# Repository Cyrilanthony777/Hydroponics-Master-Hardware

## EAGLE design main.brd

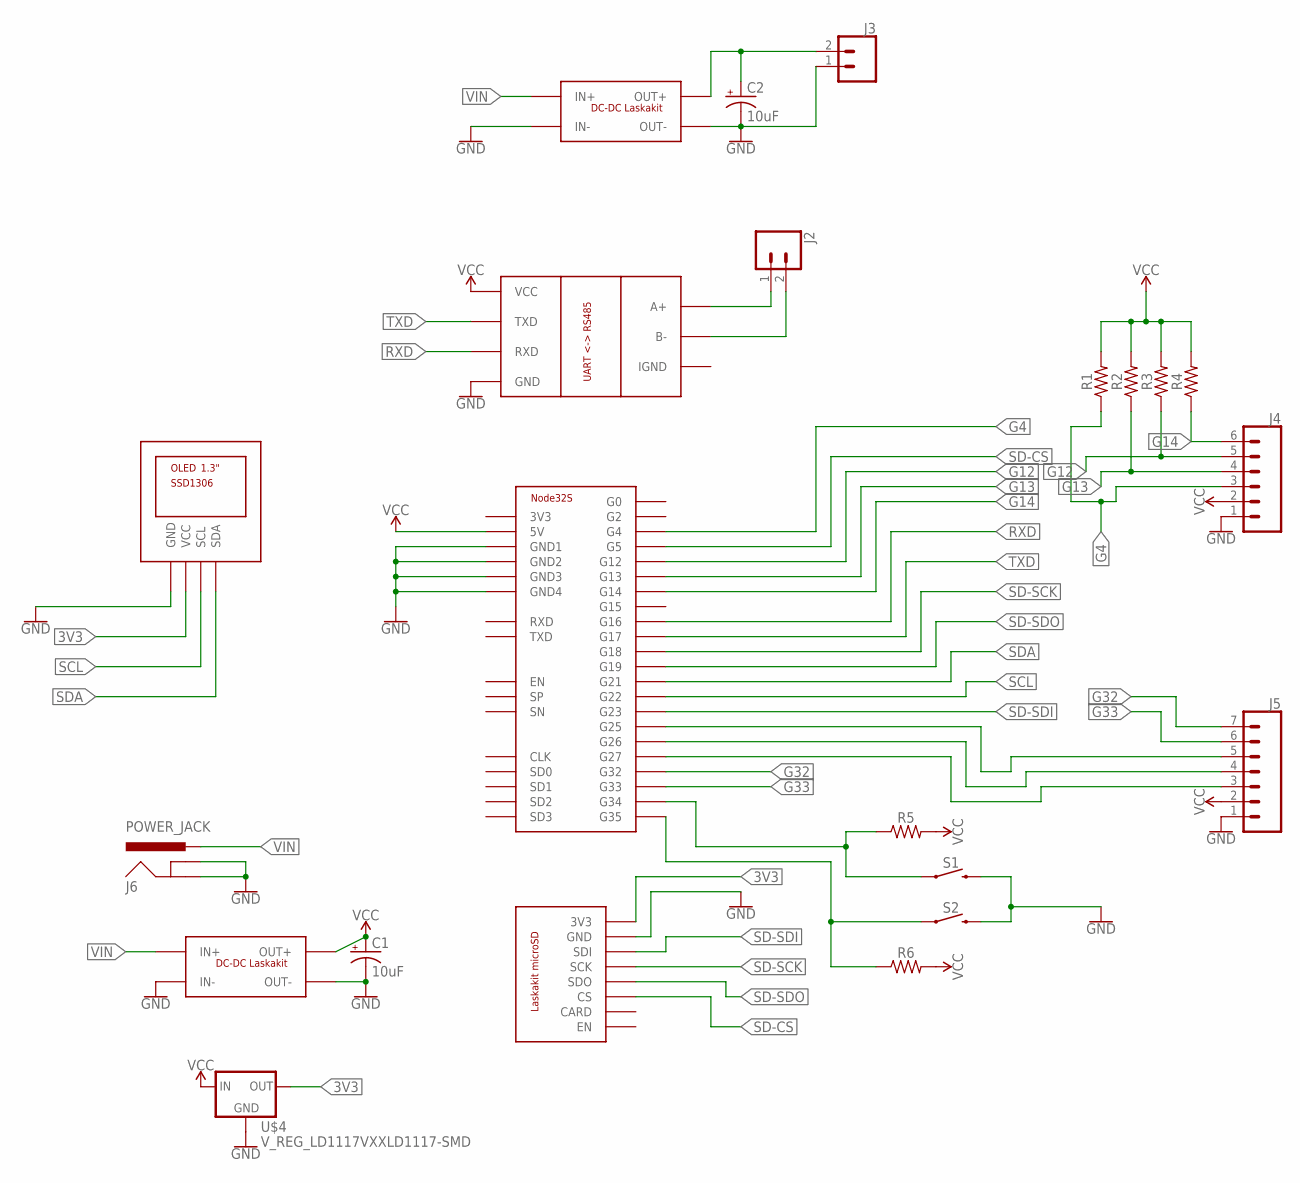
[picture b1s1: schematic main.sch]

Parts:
C1, C2: 10uF; CPOL-RADIAL-2.5MM-5MM
J2, J3: CONN_025MM; SCREWTERMINAL-5MM-2
J4: CONN_06NO_SILK_FEMALE_PTH; 1X06_NO_SILK
J5: CONN_07NO_SILK; 1X07_NO_SILK
J6: POWER_JACK; POWER_JACK_PTH
R1, R2, R3, R4, R5, R6: 0805
S1, S2: MOMENTARY-SWITCH-SPST-PTH-12MM; TACTILE_SWITCH_PTH_12MM
U$1: NODE32S
U$2: LASKAKIT_SDCARD; LASKAKIT_SD_MODULE
U$3, U$7: DC-DC-LASKAKIT; DC-DC-MODULE-LASKAKIT
U$4: V_REG_LD1117VXXLD1117-SMD; SOT223
U$5: RS485-UART-CONVERTER; RS485_MODULE
U$6: OLED_0.96_I2C; OLED_0.96

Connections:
3V3: U$2.P$1 (3V3), U$4.2 (OUT), U$6.P$2 (VCC)
G4: J4.3, R1.1, U$1.P$26 (G4)
G12: J4.5, R3.1, U$1.P$13 (G12)
G13: J4.4, R2.1, U$1.P$15 (G13)
G14: J4.6, R4.1, U$1.P$12 (G14)
G32: J5.7, U$1.P$7 (G32)
G33: J5.6, U$1.P$8 (G33)
GND: C1.2 (-), C2.2 (-), J3.1, J4.1, J5.1, J6.GND, J6.GNDBREAK, S1.3 (2), S2.3 (2), U$1.P$14 (GND1), U$1.P$18 (GND2), U$1.P$32 (GND3), U$1.P$38 (GND4), U$2.P$2 (GND), U$3.IN-, U$3.OUT-, U$4.1 (GND), U$5.GND, U$6.P$1 (GND), U$7.IN-, U$7.OUT-
unnamed: J2.1, U$5.A+
unnamed: J2.2, U$5.B-
unnamed: J5.5, U$1.P$9 (G25)
unnamed: J5.4, U$1.P$10 (G26)
unnamed: J5.3, U$1.P$11 (G27)
unnamed: C2.1 (+), J3.2, U$7.OUT+
unnamed: R6.1, S2.1, U$1.P$6 (G35)
unnamed: R5.1, S1.1, U$1.P$5 (G34)
RXD: U$1.P$27 (G16), U$5.RXD
SCL: U$1.P$36 (G22), U$6.P$3 (SCL)
SD-CS: U$1.P$29 (G5), U$2.P$6 (CS)
SD-SCK: U$1.P$30 (G18), U$2.P$4 (SCK)
SD-SDI: U$1.P$37 (G23), U$2.P$3 (SDI)
SD-SDO: U$1.P$31 (G19), U$2.P$5 (SDO)
SDA: U$1.P$33 (G21), U$6.P$4 (SDA)
TXD: U$1.P$28 (G17), U$5.TXD
VCC: C1.1 (+), J4.2, J5.2, R1.2, R2.2, R3.2, R4.2, R5.2, R6.2, U$1.P$19 (5V), U$3.OUT+, U$4.3 (IN), U$5.VCC
VIN: J6.PWR, U$3.IN+, U$7.IN+

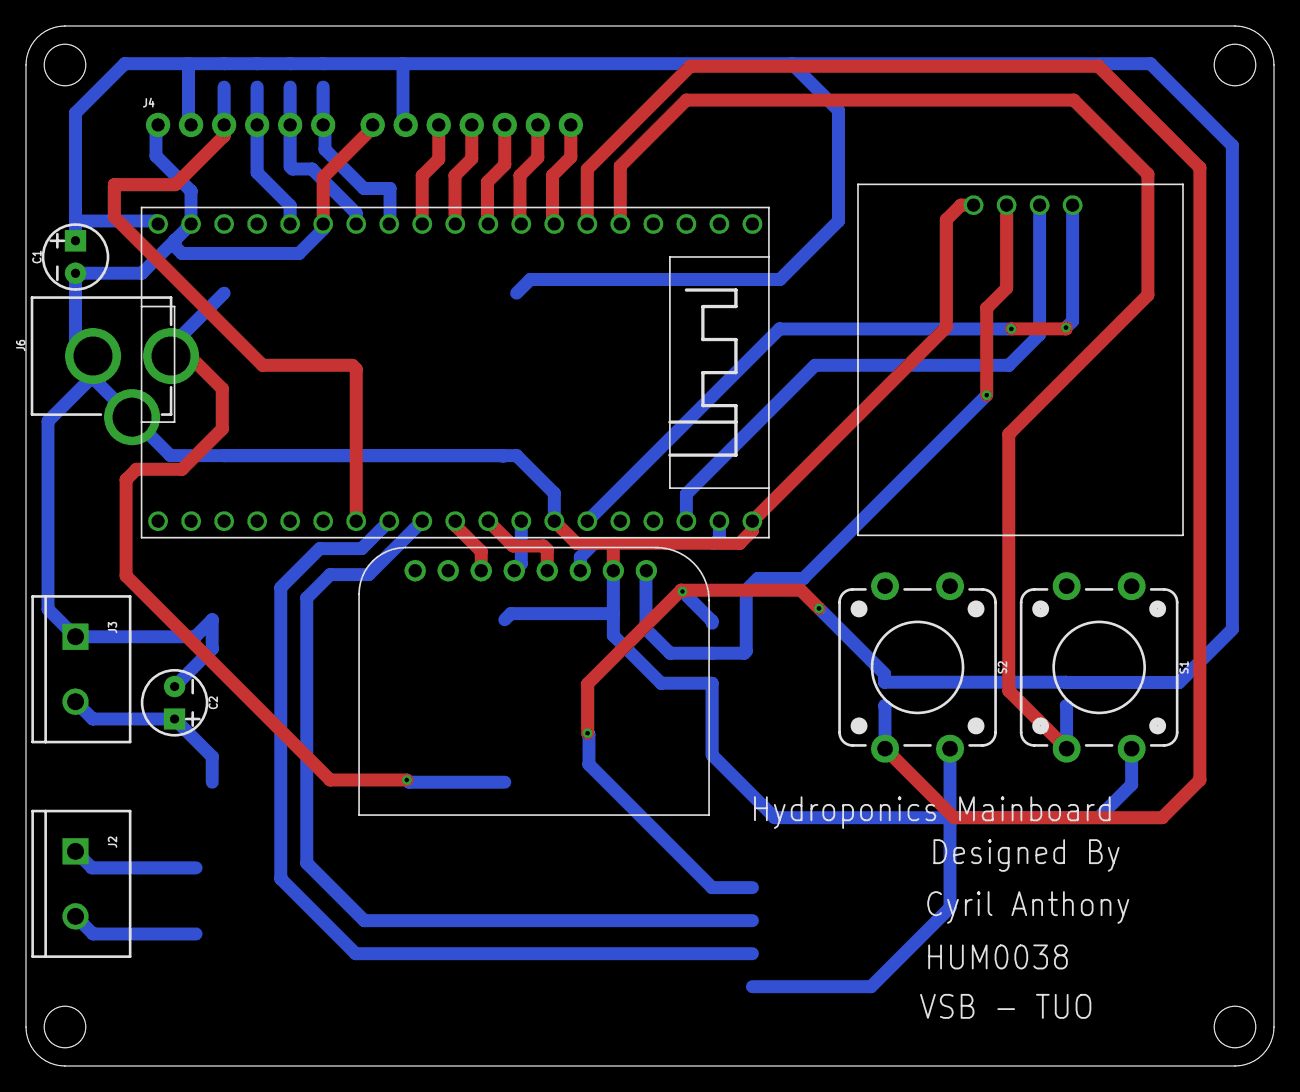
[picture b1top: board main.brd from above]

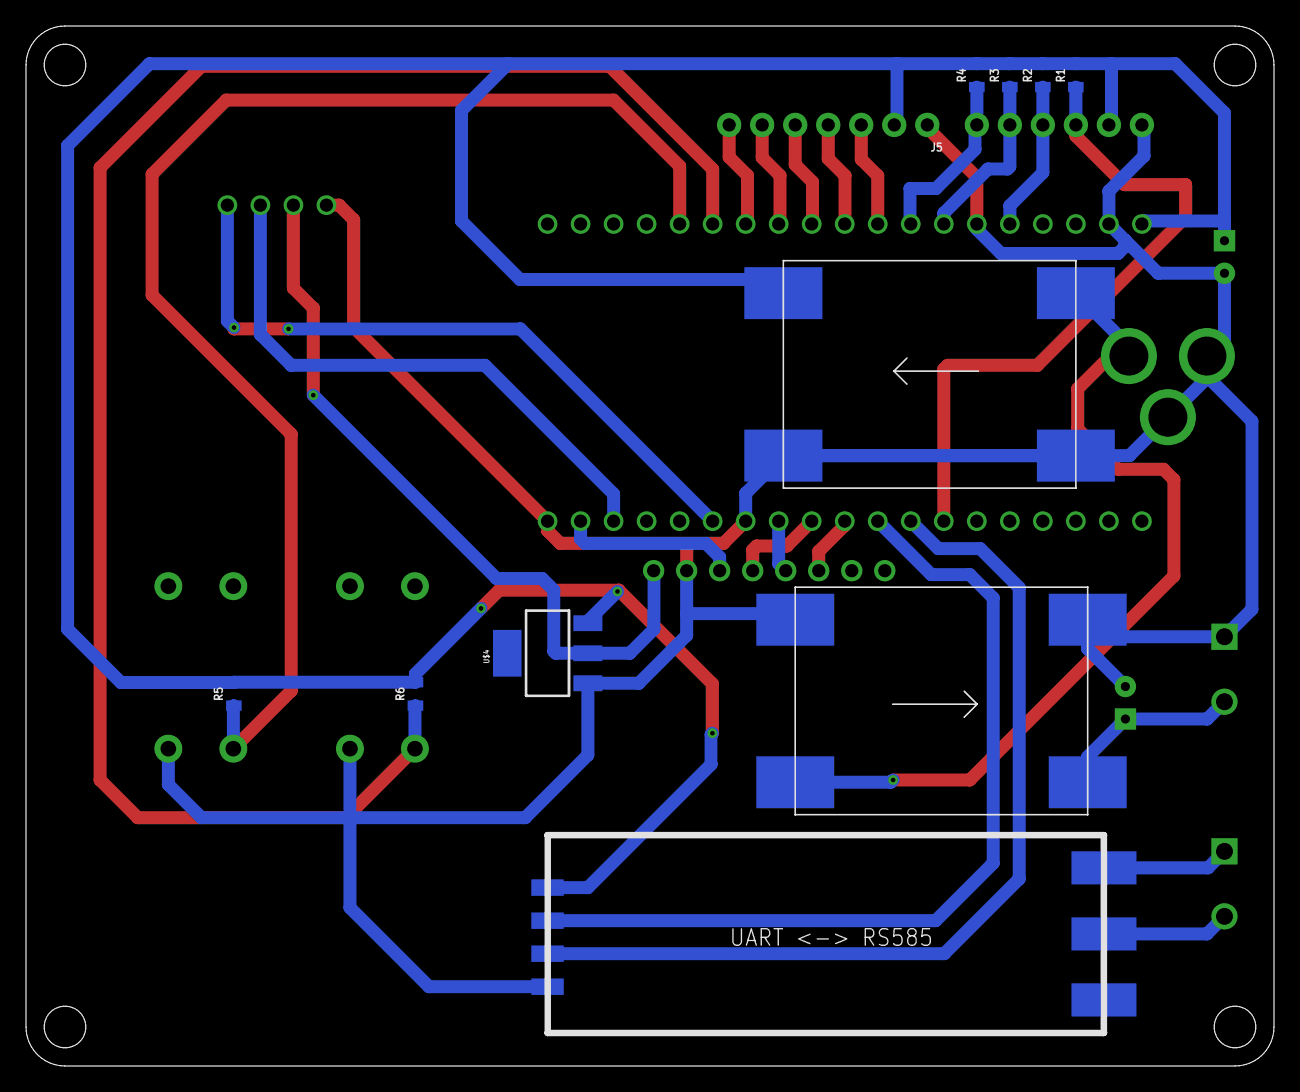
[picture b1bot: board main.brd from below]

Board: 2 copper layers, 96.0 x 80.0 mm, 22 parts (11 on the bottom side), 26 nets.

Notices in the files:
parts and their libraries:
SparkFun-Capacitors: Licensing: Creative Commons ShareAlike 4.0 International - https://creativecommons.org/licenses/by-sa/4.0
